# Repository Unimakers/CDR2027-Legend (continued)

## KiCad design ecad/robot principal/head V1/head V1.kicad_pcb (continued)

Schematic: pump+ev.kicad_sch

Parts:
C56, C57: 100nF; C_0805_2012Metric_Pad1.18x1.45mm_HandSolder
D15: SS14; D_SMA
IC2: RZ7889; SOIC127P600X175-8N; Manufacturer_Part_Number RZ7889
J29: pump+ev; Molex_KK-254_AE-6410-04A_1x04_P2.54mm_Vertical
Q1: AO3400A; SOT-23
R45: 270; R_0805_2012Metric_Pad1.20x1.40mm_HandSolder
R46: 10K; R_0805_2012Metric_Pad1.20x1.40mm_HandSolder

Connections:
+5VP2: D15.1 (K), J29.3; also elsewhere on the board
+12V1: C56.1, IC2.4 (VCC); also elsewhere on the board
/actionneurs/EV1: R45.2; also elsewhere on the board
/actionneurs/PuEv 1/ev-: D15.2 (A), J29.4, Q1.3 (D)
/actionneurs/PuEv 1/pumpA: C57.1, IC2.7 (BO_1), IC2.8 (BO_2), J29.1
/actionneurs/PuEv 1/pumpB: C57.2, IC2.5 (FO_1), IC2.6 (FO_2), J29.2
/actionneurs/pump1: IC2.2 (FI); also elsewhere on the board
GND: C56.2, IC2.1 (BI), IC2.3 (GND), Q1.2 (S), R46.2; also elsewhere on the board
unnamed: Q1.1 (G), R45.1, R46.1

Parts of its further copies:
C58, C59, C60, C61, C62, C63, C64, C65, C66, C67, C68, C69, C70, C71: 100nF; C_0805_2012Metric_Pad1.18x1.45mm_HandSolder
D16, D17, D18, D19, D20, D21, D22: SS14; D_SMA
IC3, IC4, IC5, IC6, IC7, IC8, IC9: RZ7889; SOIC127P600X175-8N; Manufacturer_Part_Number RZ7889
J30, J31, J32, J33, J34, J35, J36: pump+ev; Molex_KK-254_AE-6410-04A_1x04_P2.54mm_Vertical
Q2, Q3, Q4, Q5, Q6, Q7, Q8: AO3400A; SOT-23
R47, R49, R51, R53, R55, R57, R59: 270; R_0805_2012Metric_Pad1.20x1.40mm_HandSolder
R48, R50, R52, R54, R56, R58, R60: 10K; R_0805_2012Metric_Pad1.20x1.40mm_HandSolder

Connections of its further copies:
+5VP2: D16.1 (K), D17.1 (K), D18.1 (K), D19.1 (K), D20.1 (K), D21.1 (K), D22.1 (K), J30.3, J31.3, J32.3, J33.3, J34.3, J35.3, J36.3; also elsewhere on the board
+12V1: C58.1, C60.1, C62.1, C64.1, C66.1, C68.1, C70.1, IC3.4 (VCC), IC4.4 (VCC), IC5.4 (VCC), IC6.4 (VCC), IC7.4 (VCC), IC8.4 (VCC), IC9.4 (VCC); also elsewhere on the board
/actionneurs/EV2: R47.2; also elsewhere on the board
/actionneurs/EV3: R49.2; also elsewhere on the board
/actionneurs/EV4: R51.2; also elsewhere on the board
/actionneurs/EV5: R53.2; also elsewhere on the board
/actionneurs/EV6: R55.2; also elsewhere on the board
/actionneurs/EV7: R57.2; also elsewhere on the board
/actionneurs/EV8: R59.2; also elsewhere on the board
/actionneurs/PuEv 2/ev-: D16.2 (A), J30.4, Q2.3 (D)
/actionneurs/PuEv 2/pumpA: C59.1, IC3.7 (BO_1), IC3.8 (BO_2), J30.1
/actionneurs/PuEv 2/pumpB: C59.2, IC3.5 (FO_1), IC3.6 (FO_2), J30.2
/actionneurs/PuEv 3/ev-: D17.2 (A), J31.4, Q3.3 (D)
/actionneurs/PuEv 3/pumpA: C61.1, IC4.7 (BO_1), IC4.8 (BO_2), J31.1
/actionneurs/PuEv 3/pumpB: C61.2, IC4.5 (FO_1), IC4.6 (FO_2), J31.2
/actionneurs/PuEv 4/ev-: D18.2 (A), J32.4, Q4.3 (D)
/actionneurs/PuEv 4/pumpA: C63.1, IC5.7 (BO_1), IC5.8 (BO_2), J32.1
/actionneurs/PuEv 4/pumpB: C63.2, IC5.5 (FO_1), IC5.6 (FO_2), J32.2
/actionneurs/PuEv 5/ev-: D19.2 (A), J33.4, Q5.3 (D)
/actionneurs/PuEv 5/pumpA: C65.1, IC6.7 (BO_1), IC6.8 (BO_2), J33.1
/actionneurs/PuEv 5/pumpB: C65.2, IC6.5 (FO_1), IC6.6 (FO_2), J33.2
/actionneurs/PuEv 6/ev-: D20.2 (A), J34.4, Q6.3 (D)
/actionneurs/PuEv 6/pumpA: C67.1, IC7.7 (BO_1), IC7.8 (BO_2), J34.1
/actionneurs/PuEv 6/pumpB: C67.2, IC7.5 (FO_1), IC7.6 (FO_2), J34.2
/actionneurs/PuEv 7/ev-: D21.2 (A), J35.4, Q7.3 (D)
/actionneurs/PuEv 7/pumpA: C69.1, IC8.7 (BO_1), IC8.8 (BO_2), J35.1
/actionneurs/PuEv 7/pumpB: C69.2, IC8.5 (FO_1), IC8.6 (FO_2), J35.2
/actionneurs/PuEv 8/ev-: D22.2 (A), J36.4, Q8.3 (D)
/actionneurs/PuEv 8/pumpA: C71.1, IC9.7 (BO_1), IC9.8 (BO_2), J36.1
/actionneurs/PuEv 8/pumpB: C71.2, IC9.5 (FO_1), IC9.6 (FO_2), J36.2
/actionneurs/pump2: IC3.2 (FI); also elsewhere on the board
/actionneurs/pump3: IC4.2 (FI); also elsewhere on the board
/actionneurs/pump4: IC5.2 (FI); also elsewhere on the board
/actionneurs/pump5: IC6.2 (FI); also elsewhere on the board
/actionneurs/pump6: IC7.2 (FI); also elsewhere on the board
/actionneurs/pump7: IC8.2 (FI); also elsewhere on the board
/actionneurs/pump8: IC9.2 (FI); also elsewhere on the board
GND: C58.2, C60.2, C62.2, C64.2, C66.2, C68.2, C70.2, IC3.1 (BI), IC3.3 (GND), IC4.1 (BI), IC4.3 (GND), IC5.1 (BI), IC5.3 (GND), IC6.1 (BI), IC6.3 (GND), IC7.1 (BI), IC7.3 (GND), IC8.1 (BI), IC8.3 (GND), IC9.1 (BI), IC9.3 (GND), Q2.2 (S), Q3.2 (S), Q4.2 (S), Q5.2 (S), Q6.2 (S), Q7.2 (S), Q8.2 (S), R48.2, R50.2, R52.2, R54.2, R56.2, R58.2, R60.2; also elsewhere on the board
unnamed: Q2.1 (G), R47.1, R48.1
unnamed: Q3.1 (G), R49.1, R50.1
unnamed: Q4.1 (G), R51.1, R52.1
unnamed: Q5.1 (G), R53.1, R54.1
unnamed: Q6.1 (G), R55.1, R56.1
unnamed: Q7.1 (G), R57.1, R58.1
unnamed: Q8.1 (G), R59.1, R60.1

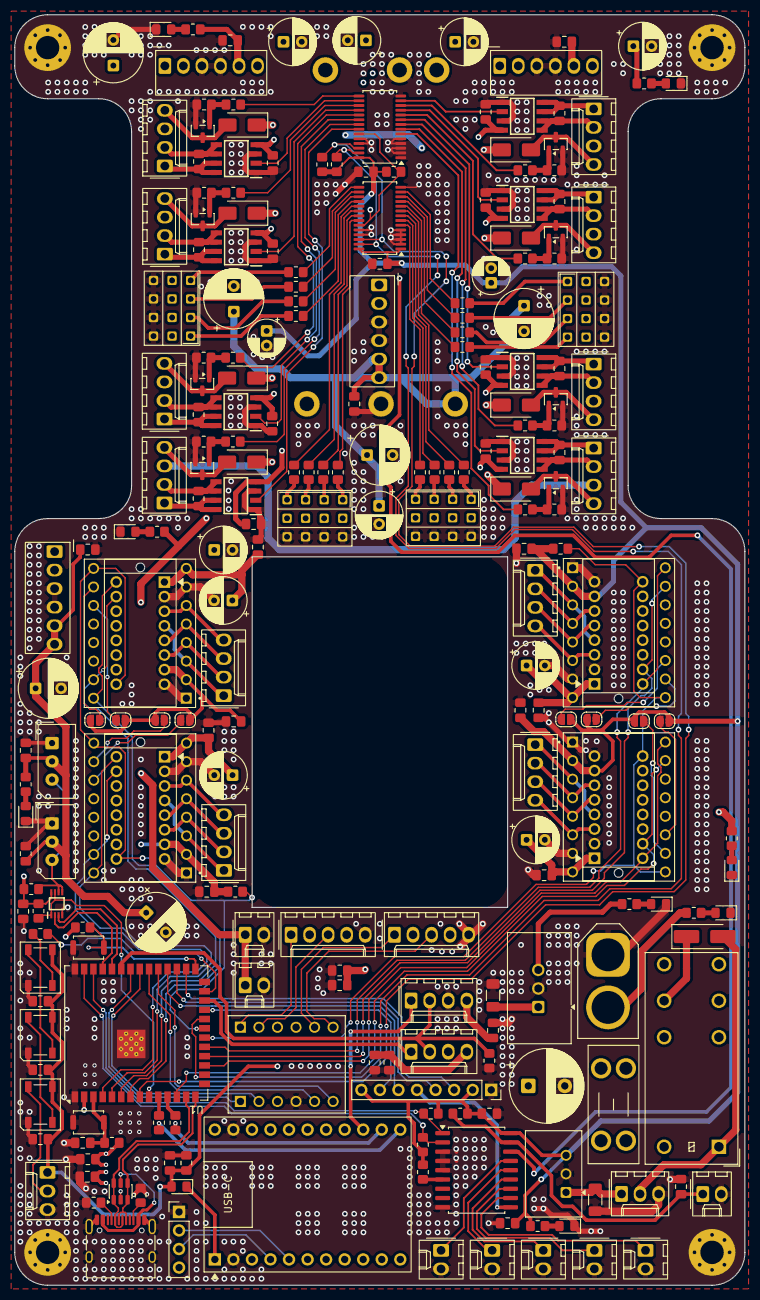
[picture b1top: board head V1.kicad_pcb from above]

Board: 4 copper layers, 100.0 x 174.0 mm, 241 parts (1 on the bottom side), 184 nets.

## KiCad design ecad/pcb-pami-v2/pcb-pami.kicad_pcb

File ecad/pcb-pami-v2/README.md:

# PCBete

Carte électronique des PAMI (petits robots autonomes) pour la Coupe de France de Robotique 2027.

Ce dossier contient la **nouvelle carte** (2 couches, simplifiée, en cours de conception). L'ancienne carte, celle des PAMI actuels, est dans l'historique Git (commit `070d910`, 2026-09-11) ; sa description est dans `.claude/skills/electronique-pami/SKILL.md`.

## Fonctions de la nouvelle carte (état du schéma, 2026-11-17)

Carte autour d'un ESP32-S3-WROOM-1 (empreinte WROOM-1U, antenne externe) :
- 2 NEMA 17 (28 V, 2 A max), 2 drivers TMC2209 SilentStepStick (U8, U9)
- 1 moteur DC (3 à 20 V, 3 A max) avec un driver RZ7899 (U1), un seul sens de rotation
- 2 servomoteurs 5 V (J23, J26)
- 1 capteur ToF VL53L0X en I2C (J2) et 1 MPU en I2C (MPU1)
- 1 écran TFT en SPI (J3)
- 1 module radio RFM69HCW en SPI (J17, empreinte à créer)
- LED NeoPixel embarquée (D6) et connecteur pour une guirlande (J8, 60 mA/LED)
- Arrêt d'urgence de puissance (30 V, 12 A max) par P-MOS commandé depuis J9
- Bouton d'équipe jaune/bleu (J5) et tirette de lancement (J7)
- USB-C (J1) pour la programmation seulement
- Tout est piloté directement par l'ESP32 : plus d'extenseur d'entrées/sorties (MCP23008)

Retiré par rapport à l'ancienne carte : MCP23008, 2 LTC4412 et leurs P-MOS, 2e driver DC, 3 des 4 ToF, capteurs AS5600, LiDAR (UART0), liaison Luckfox (UART1), mesure de la tension batterie.

## Format

- Carte **2 couches** (F.Cu et B.Cu, 1,6 mm), plus simple à router mais avec moins de place. Plus de plans internes.
- Contour **60 × 50 mm**, angles arrondis R3,5, de (30 ; 25) à (90 ; 75) dans KiCad. Pas de trou central.
- 4 trous M3 prévus (H1 à H4) ; H2 n'est pas encore posé dans le PCB.
- **Non routée** : placement en cours, 17 composants encore posés hors du contour (connecteurs J5, J7, J8, J9, J12, U1, PMOS du BAU, U4, condensateurs). Un second rectangle de 70 × 50 mm tracé sur Edge.Cuts en (25 ; 80) est vide.

## Alimentation

- Batterie LiPo 12 V (20 V max) sur XT30 (J6), puis coupure par le P-MOS AO4407A4 commandé par l'arrêt d'urgence (J9).
- Le 5 V est produit sur la carte par un buck AP63300 (3 A, entrée 3,8 à 32 V, après le BAU). Sortie réglée par R16/R17 : 0,8 × (1 + 27k/5,1k) = 5,04 V. Valeurs à vérifier sur la datasheet avant commande.
- Deux diodes SS34 font un OU entre le 5 V du buck (D3) et le 5 V de l'USB-C (D2) vers `VCC_5V_GLOBAL`. L'USB-C ne sert qu'à programmer sans batterie : en USB seul, le 5 V tombe vers 4,6 V.
- 3,3 V par un AMS1117-3.3 (U4).

## Reste à faire

- Relier à un GPIO de l'ESP32 : reset écran (`RST`), `TEAM_BTN`, `LAUNCHPULL`, `XSHUT0` et `GPIOX` du ToF, `EN` des TMC2209.
- Empreinte de J17 (radio), trou H2, finir le placement, puis router.
- Vérifier la LED D1 (valeur vide), l'empreinte de L1 (XAL5050-682MEC prévue) et la ligne DATA du NeoPixel sur J8.

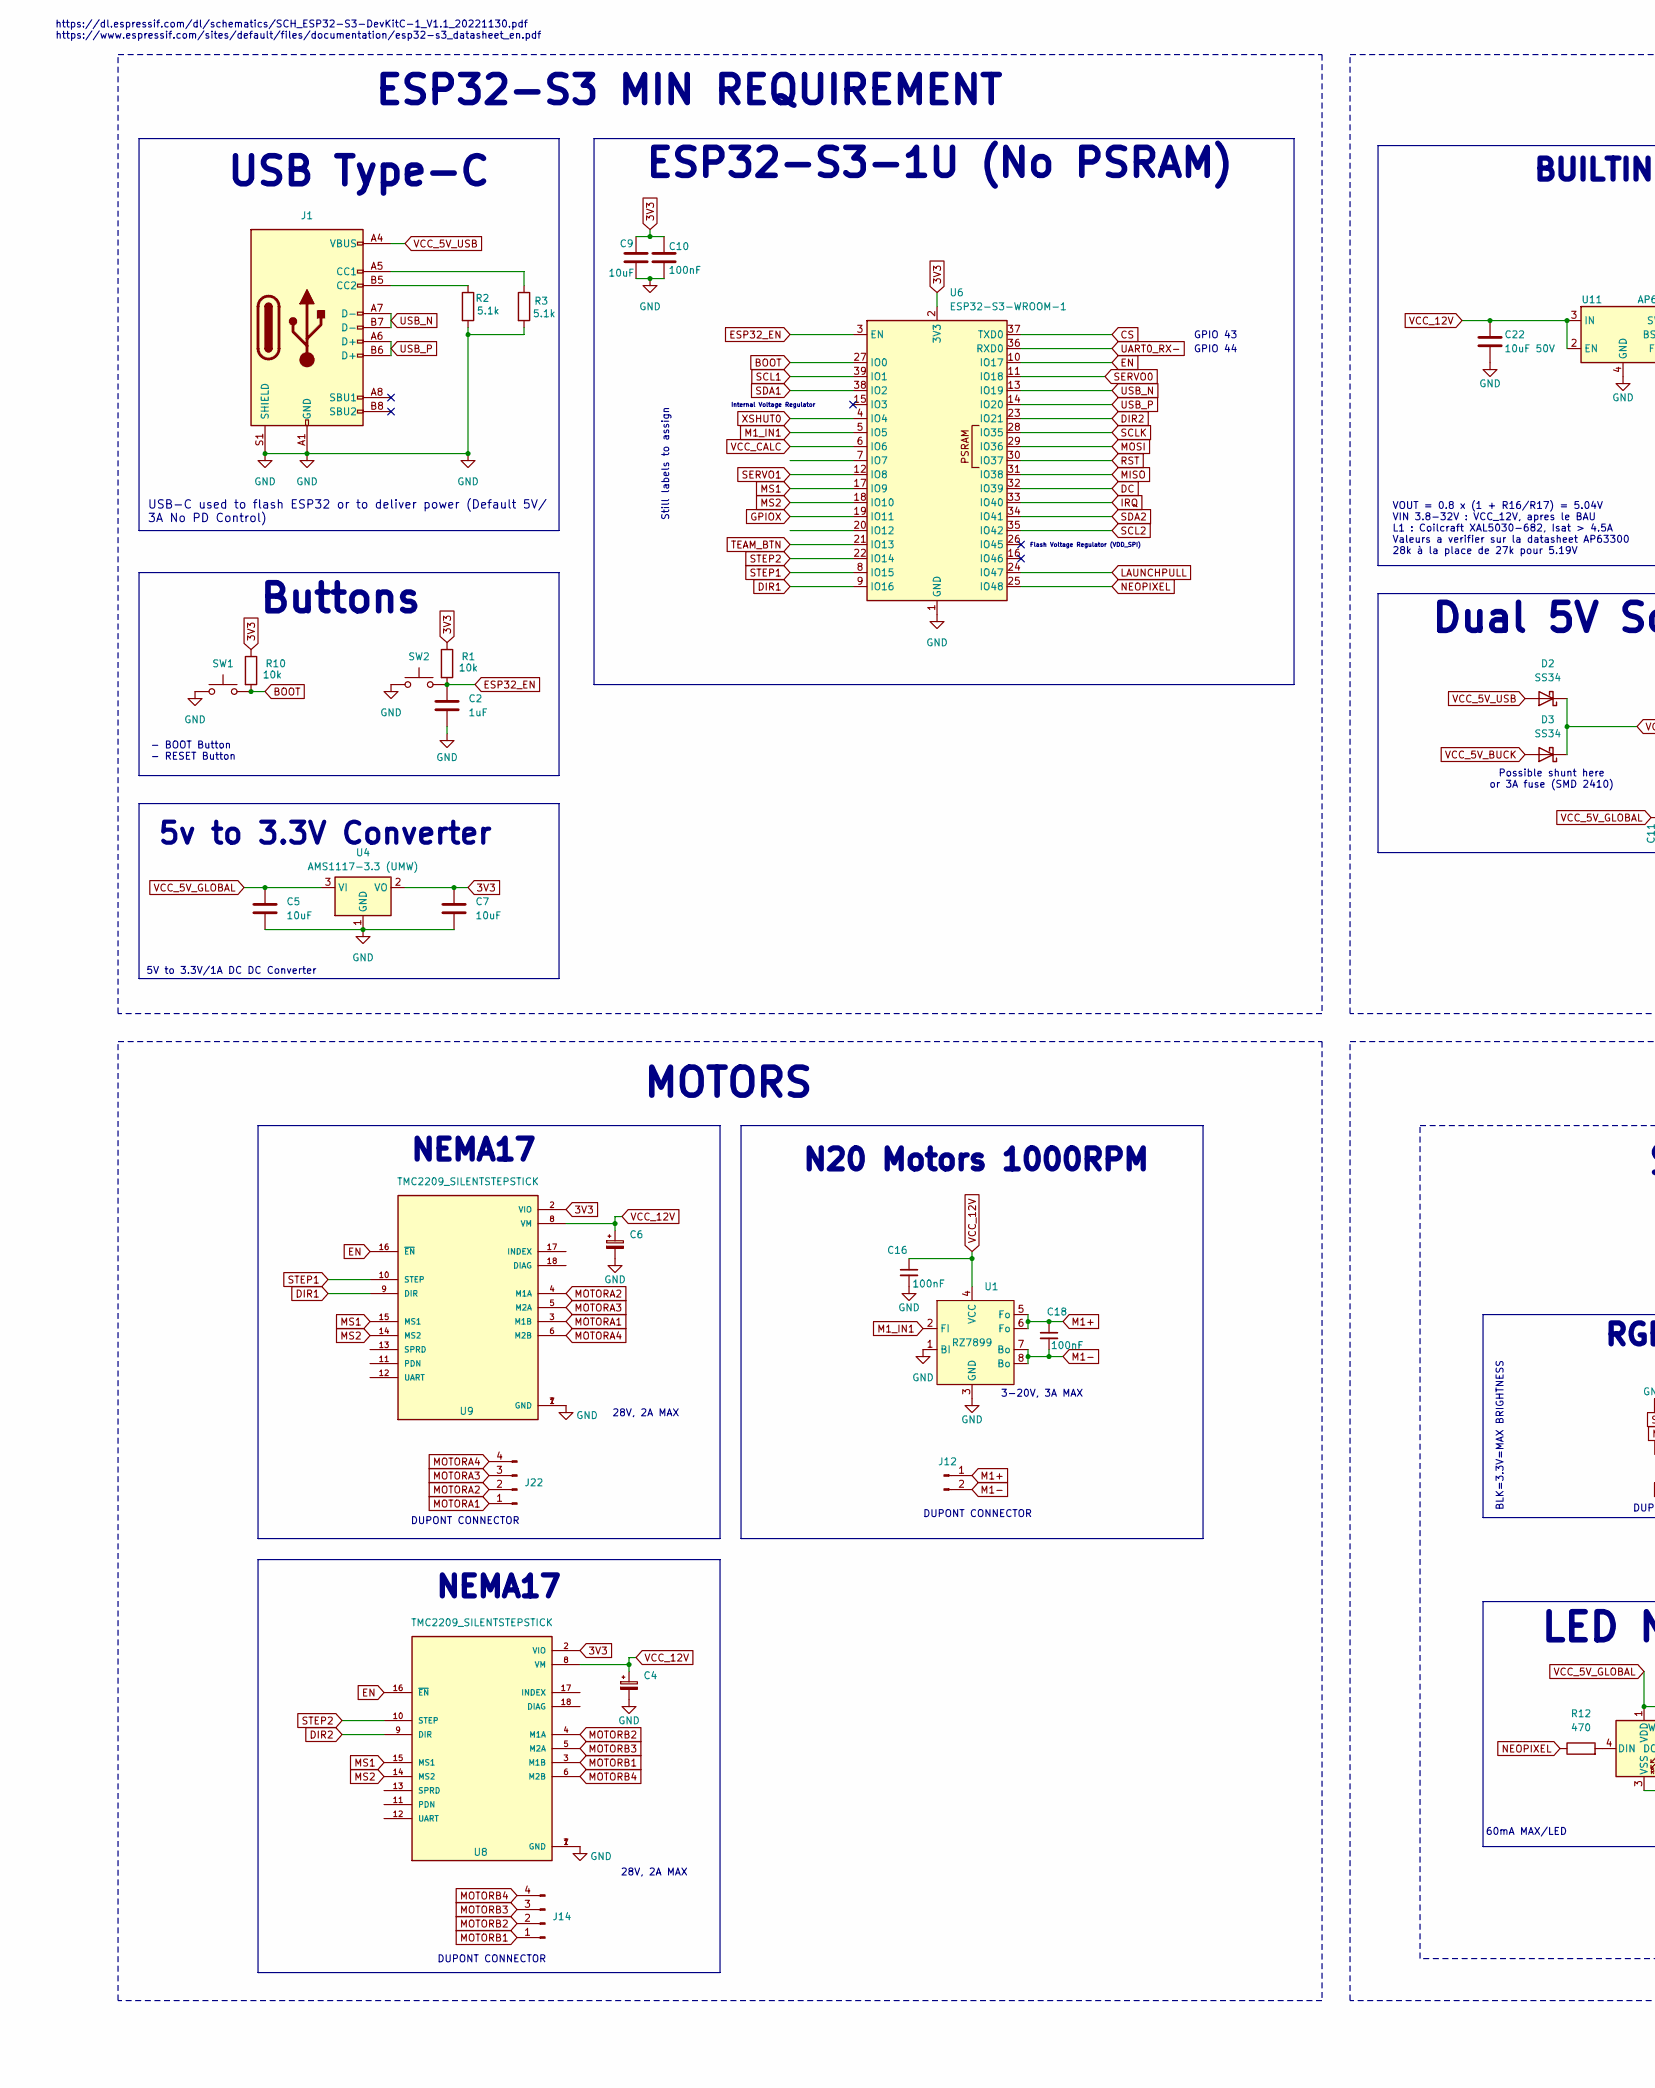
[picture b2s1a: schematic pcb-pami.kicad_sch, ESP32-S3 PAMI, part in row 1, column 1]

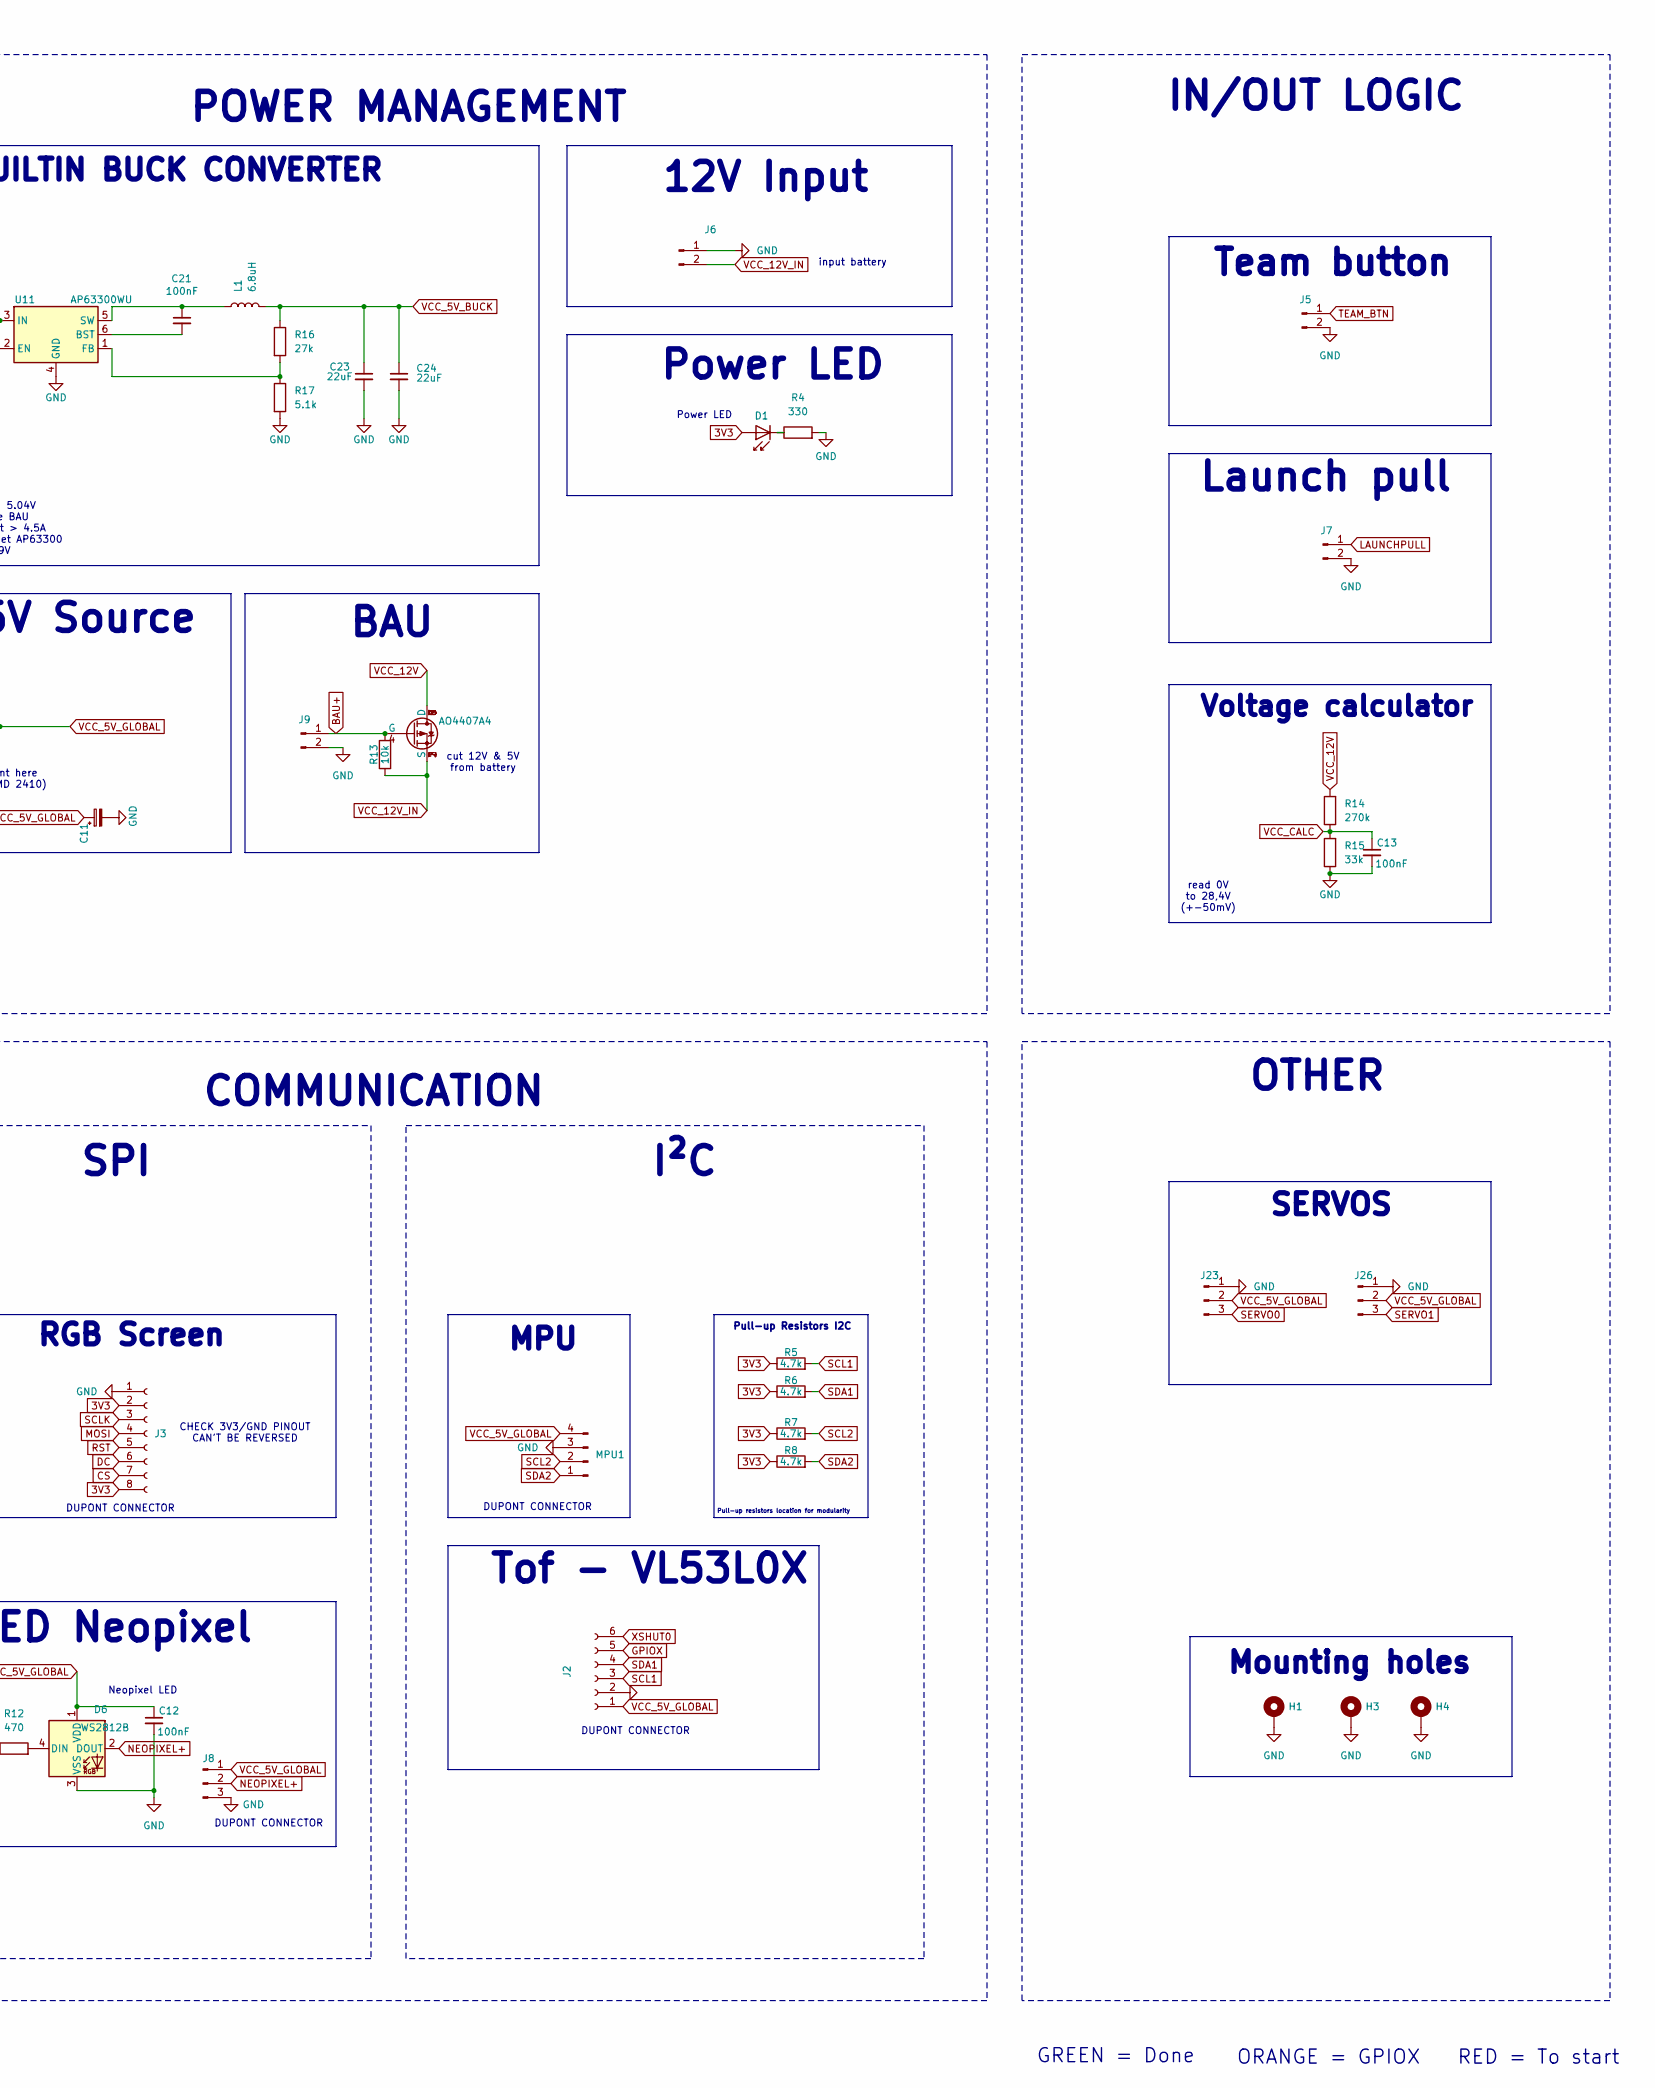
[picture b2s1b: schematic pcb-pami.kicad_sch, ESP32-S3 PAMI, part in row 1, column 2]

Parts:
AO4407A4: PMOS; SOIC-8-1EP_3.9x4.9mm_P1.27mm_EP2.29x3mm_ThermalVias
C2: 1uF; C_0805_2012Metric_Pad1.18x1.45mm_HandSolder
C4, C6: 100u; C_Radial_D8.0mm_H11.5mm_P3.50mm
C5, C7, C9: 10uF; C_0805_2012Metric_Pad1.18x1.45mm_HandSolder
C10, C12, C13, C16, C18, C21: 100nF; C_0805_2012Metric_Pad1.18x1.45mm_HandSolder
C11: 470u; C_Radial_D8.0mm_H11.5mm_P3.50mm
C22: 10uF 50V; C_1206_3216Metric_Pad1.33x1.80mm_HandSolder
C23, C24: 22uF; C_1206_3216Metric_Pad1.33x1.80mm_HandSolder
D1: LED_0805_2012Metric_Pad1.15x1.40mm_HandSolder
D2, D3: SS34; D_SMA
D6: WS2812B; LED_WS2812B_PLCC4_5.0x5.0mm_P3.2mm
H1, H3, H4: MountingHole_Pad; MountingHole_3.2mm_M3_Pad
J1: USB_C_Receptacle_USB2.0_16P; USB_C_Receptacle_GCT_USB4105-xx-A_16P_TopMnt_Horizontal
J2: Conn_01x06_Socket; PinHeader_1x06_P2.54mm_Vertical
J3: Conn_01x08_Socket; PinSocket_1x08_P2.54mm_Vertical
J5, J7, J9, J12: Conn_01x02_Pin; PinHeader_1x02_P2.54mm_Vertical
J6: Conn_01x02_Pin; AMASS_XT30U-F_1x02_P5.0mm_Vertical
J8, J23, J26: Conn_01x03_Pin; PinHeader_1x03_P2.54mm_Vertical
J14, J22: Conn_01x04_Pin; PinHeader_1x04_P2.54mm_Vertical
L1: 6.8uH; L_Coilcraft_XAL5030-XXX
MPU1: Conn_01x04_Pin; PinHeader_1x04_P2.54mm_Vertical
R1, R10, R13: 10k; R_0805_2012Metric_Pad1.20x1.40mm_HandSolder
R2, R3, R17: 5.1k; R_0805_2012Metric_Pad1.20x1.40mm_HandSolder
R4: 330; R_0805_2012Metric_Pad1.20x1.40mm_HandSolder
R5, R6, R7, R8: 4.7k; R_0805_2012Metric_Pad1.20x1.40mm_HandSolder
R12: 470; R_0805_2012Metric_Pad1.20x1.40mm_HandSolder
R14: 270k; R_0805_2012Metric_Pad1.20x1.40mm_HandSolder
R15: 33k; R_0805_2012Metric_Pad1.20x1.40mm_HandSolder
R16: 27k; R_0805_2012Metric_Pad1.20x1.40mm_HandSolder
SW1, SW2: SW_Push; SW_Push_SPST_NO_Alps_SKRK
U1: RZ7899; SOIC-8_3.9x4.9mm_P1.27mm
U4: AMS1117-3.3 (UMW); SOT-223-3_TabPin2
U6: ESP32-S3-WROOM-1; ESP32-S3-WROOM-1U
U8, U9: TMC2209_SILENTSTEPSTICK; MODULE_TMC2209_SILENTSTEPSTICK; PARTREV 1.20
U11: AP63300WU; TSOT-23-6

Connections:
3V3: C7.1, C9.1, C10.1, D1.2 (A), J3.2, J3.8, R1.1, R5.1, R6.1, R7.1, R8.1, R10.1, U4.2 (VO), U6.2 (3V3), U8.2 (VIO), U9.2 (VIO)
BAU+: AO4407A4.4 (G), J9.1, R13.2
BOOT: R10.2, SW1.2, U6.27 (IO0)
CS: J3.7, U6.37 (TXD0)
DC: J3.6, U6.32 (IO39)
DIR1: U6.9 (IO16), U9.9 (DIR)
DIR2: U6.23 (IO21), U8.9 (DIR)
EN: U6.10 (IO17), U8.16 (~EN), U9.16 (~EN)
ESP32_EN: C2.1, R1.2, SW2.2, U6.3 (EN)
GND: C2.2, C4.2, C5.2, C6.2, C7.2, C9.2, C10.2, C11.2, C12.2, C13.2, C16.2, C22.2, C23.2, C24.2, D6.3 (VSS), H1.1 (1_1), H3.1 (1_1), H4.1 (1_1), J1.A1 (GND), J1.A12 (GND), J1.B1 (GND), J1.B12 (GND), J1.S1 (SHIELD), J2.2, J3.1, J5.2, J6.1, J7.2, J8.3, J9.2, J23.1, J26.1, MPU1.3, R2.2, R3.2, R4.2, R15.1, R17.2, SW1.1, SW2.1, U1.1 (BI), U1.3 (GND), U4.1 (GND), U6.1 (GND), U6.40 (GND), U6.41 (GND), U8.1 (GND), U8.7 (GND), U9.1 (GND), U9.7 (GND), U11.4 (GND)
GPIOX: J2.5, U6.19 (IO11)
IRQ: U6.33 (IO40)
LAUNCHPULL: J7.1, U6.24 (IO47)
M1+: C18.1, J12.1, U1.5 (Fo), U1.6 (Fo)
M1-: C18.2, J12.2, U1.7 (Bo), U1.8 (Bo)
M1_IN1: U1.2 (FI), U6.5 (IO5)
MISO: U6.31 (IO38)
MOSI: J3.4, U6.29 (IO36)
MOTORA1: J22.1, U9.3 (M1B)
MOTORA2: J22.2, U9.4 (M1A)
MOTORA3: J22.3, U9.5 (M2A)
MOTORA4: J22.4, U9.6 (M2B)
MOTORB1: J14.1, U8.3 (M1B)
MOTORB2: J14.2, U8.4 (M1A)
MOTORB3: J14.3, U8.5 (M2A)
MOTORB4: J14.4, U8.6 (M2B)
MS1: U6.17 (IO9), U8.15 (MS1), U9.15 (MS1)
MS2: U6.18 (IO10), U8.14 (MS2), U9.14 (MS2)
NEOPIXEL: R12.1, U6.25 (IO48)
NEOPIXEL+: D6.2 (DOUT), J8.2
unnamed: D1.1 (K), R4.1
unnamed: D6.4 (DIN), R12.2
unnamed: J1.A5 (CC1), R3.1
unnamed: J1.B5 (CC2), R2.1
unnamed: C21.2, U11.6 (BST)
unnamed: R16.2, R17.1, U11.1 (FB)
unnamed: C21.1, L1.1, U11.5 (SW)
RST: J3.5, U6.30 (IO37)
SCL1: J2.3, R5.2, U6.39 (IO1)
SCL2: MPU1.2, R7.2, U6.35 (IO42)
SCLK: J3.3, U6.28 (IO35)
SDA1: J2.4, R6.2, U6.38 (IO2)
SDA2: MPU1.1, R8.2, U6.34 (IO41)
SERVO0: J23.3, U6.11 (IO18)
SERVO1: J26.3, U6.12 (IO8)
STEP1: U6.8 (IO15), U9.10 (STEP)
STEP2: U6.22 (IO14), U8.10 (STEP)
TEAM_BTN: J5.1, U6.21 (IO13)
UART0_RX-: U6.36 (RXD0)
USB_N: J1.A7 (D-), J1.B7 (D-), U6.13 (IO19)
USB_P: J1.A6 (D+), J1.B6 (D+), U6.14 (IO20)
VCC_5V_BUCK: C23.1, C24.1, D3.2 (A), L1.2, R16.1
VCC_5V_GLOBAL: C5.1, C11.1, C12.1, D2.1 (K), D3.1 (K), D6.1 (VDD), J2.1, J8.1, J23.2, J26.2, MPU1.4, U4.3 (VI)
VCC_5V_USB: D2.2 (A), J1.A4 (VBUS), J1.A9 (VBUS), J1.B4 (VBUS), J1.B9 (VBUS)
VCC_12V: AO4407A4.5 (D), AO4407A4.6 (D), AO4407A4.7 (D), AO4407A4.8 (D), AO4407A4.9 (D), C4.1, C6.1, C16.1, C22.1, R14.2, U1.4 (VCC), U8.8 (VM), U9.8 (VM), U11.2 (EN), U11.3 (IN)
VCC_12V_IN: AO4407A4.1 (S), AO4407A4.2 (S), AO4407A4.3 (S), J6.2, R13.1
VCC_CALC: C13.1, R14.1, R15.2, U6.6 (IO6)
XSHUT0: J2.6, U6.4 (IO4)

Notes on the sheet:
USB-C used to flash ESP32 or to deliver power (Default 5V/ 3A No PD Control)
Pull-up Resistors I2C
read 0V to 28,4V (+-50mV)
Power LED
LED Neopixel
MOTORS
DUPONT CONNECTOR
IN/OUT LOGIC
Buttons
GREEN = Done
BUILTIN BUCK CONVERTER
CHECK 3V3/GND PINOUT CAN'T BE REVERSED
ESP32-S3-1U (No PSRAM)
RED = To start
BAU
Dual 5V Source
28V, 2A MAX
USB Type-C
5v to 3.3V Converter
5V to 3.3V/1A DC DC Converter
https://www.espressif.com/sites/default/files/documentation/esp32-s3_datasheet_en.pdf
NEMA17
Neopixel LED
GPIO 44
3-20V, 3A MAX
VOUT = 0.8 x (1 + R16/R17) = 5.04V VIN 3.8-32V : VCC_12V, apres le BAU L1 : Coilcraft XAL5030-682, Isat > 4.5A Valeurs a verifier sur la datasheet AP63300 28k à la place de 27k pour 5.19V
Pull-up resistors location for modularity
ESP32-S3 MIN REQUIREMENT
cut 12V & 5V from battery
Flash Voltage Regulator (VDD_SPI)
60mA MAX/LED
N20 Motors 1000RPM
I²C
GPIO 43
SPI
Team button
Tof - VL53L0X
Possible shunt here or 3A fuse (SMD 2410)
ORANGE = GPIOX
Still labels to assign

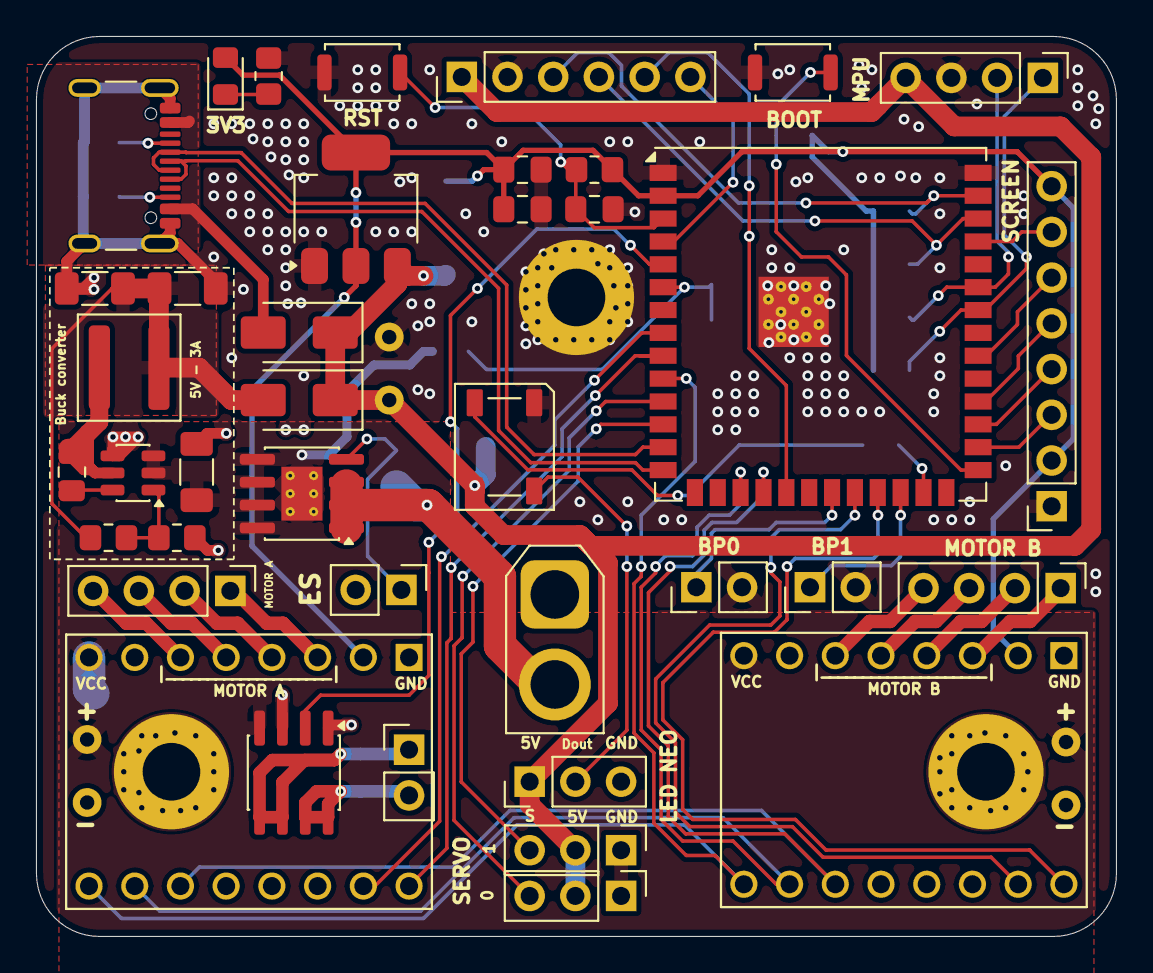
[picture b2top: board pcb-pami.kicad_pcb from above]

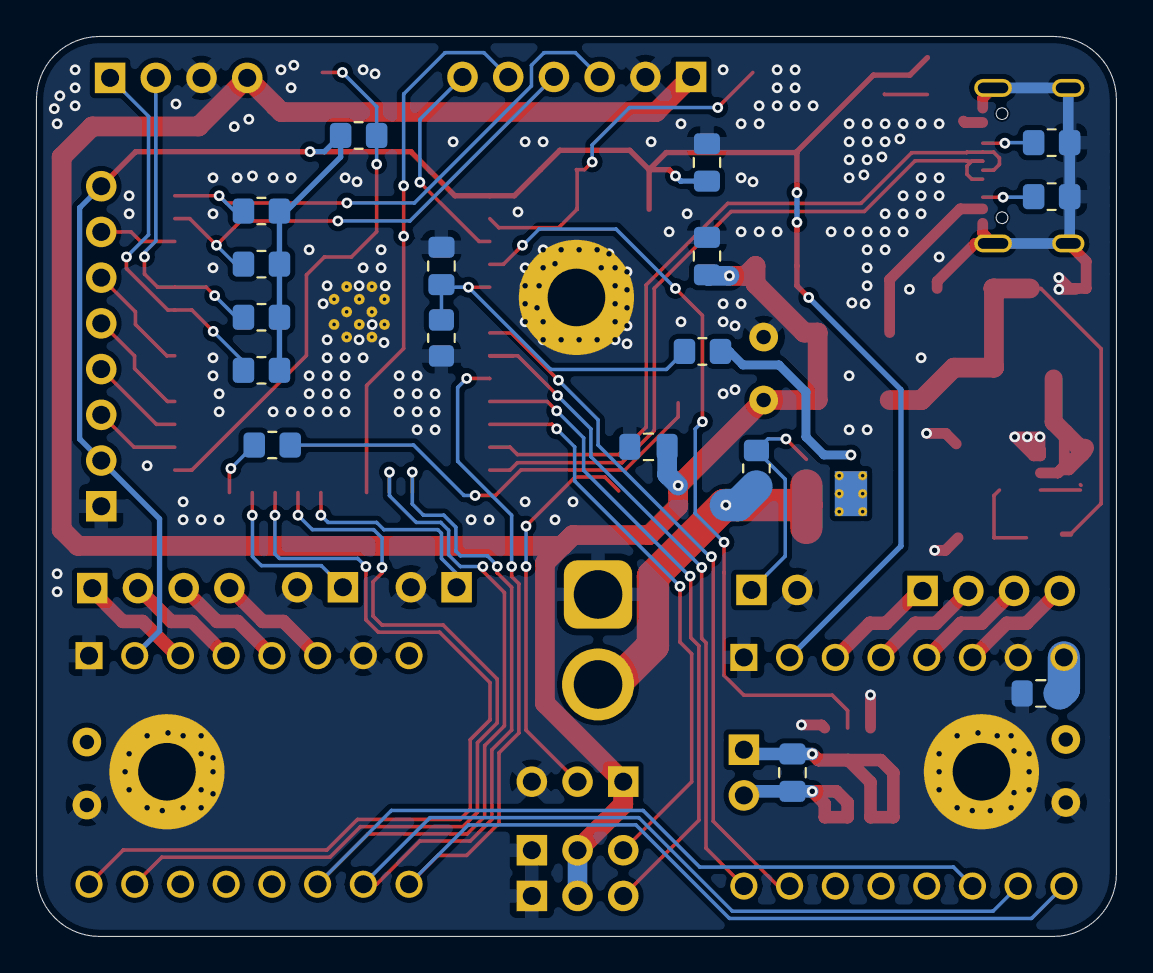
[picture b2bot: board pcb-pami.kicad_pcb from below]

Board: 2 copper layers, 60.0 x 50.0 mm, 62 parts (17 on the bottom side), 55 nets.

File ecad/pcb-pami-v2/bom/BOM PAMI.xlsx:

Nb de cartes | 13 |  | Marge appliquee seulement si 'Marge (1/0)' = 1 (resistances et condensateurs). 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
Marge R/C | 0.3
Inclure (1/0) | Refs | Valeur | Boitier | Type | Tolerance | Tension min (V) | Courant min (A) | Technologie / dielectrique | Autres contraintes | Qte/carte | Marge (1/0) | Qte a commander | Ref Mouser (a saisir) | Prix Mouser EUR | Total Mouser | Ref LCSC/JLC (a saisir) | Prix JLC USD | Total JLC | Remarque
1 | C2 | 1uF 50V X7R | 0805 | Condensateur | 10 % | 10 |  | X7R ou X5R | EN de l'ESP32 (3V3), avec R1 10k | 1 | 1 | 17 | 963-UMK212B7105KG-T | 0.099 | 1.683 |  |  |  | Taiyo Yuden 1uF 50V X7R 0805 ; stock 415 k (Mouser, 19/11/2026)
1 | C5,C7,C9 | 10uF 25V X5R | 0805 | Condensateur | 10 % | 10 |  | X5R ou X7R | Decouplage 5V/3V3 ; 16 V conseille | 3 | 1 | 51 | 963-TMK212BBJ106KG-T | 0.075 | 3.825 |  |  |  | Taiyo Yuden 10uF 25V X5R 0805 ; stock 240 k (Mouser, 19/11/2026)
1 | C10,C12,C13,C16,C21 | 100nF 50V X7R | 0805 | Condensateur | 10 % | 16 |  | X7R | Decouplage ; C21 = bootstrap du buck (BST) | 5 | 1 | 85 | 187-CL21B104KBCNNNC | 0.028 | 2.38 |  |  |  | Samsung 100nF 50V X7R 0805 ; stock 19 k (Mouser, 19/11/2026)
1 | C22 | 10uF 50V | 0805 | Condensateur | 10 % | 35 |  | X7R ou X5R | Entree buck (VIN 12 V, 20 V max) ; 50 V conseille (perte de capacite sous tensi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 | 1 | 1 | 17 | 963-UMK316BBJ106ML-T | 0.188 | 3.196 |  |  |  | EMPREINTE 1206 : Taiyo Yuden 10uF 50V X5R 1206 20 % ; stock 342 k. Les 10uF >=3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
1 | C23,C24 | 22uF 25V X5R | 0805 | Condensateur | 20 % | 10 |  | X5R ou X7R | Sortie buck 5 V ; 16 V conseille ; ESR bas | 2 | 1 | 34 | 963-TMK316BBJ226ML-T | 0.27 | 9.18 |  |  |  | EMPREINTE 1206 : Taiyo Yuden 22uF 25V X5R 1206 ; stock 102 k. En 0805, seul Tai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
1 | C4,C6 | 100uF >=35V radial D8 P3.5 | THT | Condensateur electrolytique | 20 % | 25 |  | Alu radial | Bus 12 V (20 V max) ; 35 V conseille ; D8 mm, H max 11.5 mm, pas 3.5 mm | 2 | 0 | 26 | 647-UPW1V101MPD | 0.204 | 5.304 |  |  |  | Nichicon UPW 100uF 35V 105C low-Z, D8 x 11.5, pas 3.5 (verifie), vrac ; stock 5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
1 | C11 | 470uF >=10V radial D8 P3.5 | THT | Condensateur electrolytique | 20 % | 10 |  | Alu radial | Bus 5 V ; 16 V conseille ; D8 mm, H max 11.5 mm, pas 3.5 mm | 1 | 0 | 13 | 647-UVR1C471MPD1TD | 0.167 | 2.171 |  |  |  | Nichicon UVR 470uF 16V 85C, D8 x 11.5, pas 3.5 (verifie) ; stock 4 742. Version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
1 | D2,D3 | SS34 Schottky 40V 3A | SMA | Diode Schottky |  | 20 | 3 | Schottky | OU de sources 5 V (USB / buck) ; Vrrm >= 20 V (40 V conseille), If >= 3 A, Vf b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 | 2 | 0 | 26 | 821-SS34 | 0.339 | 8.814 |  |  |  | Taiwan Semi SS34 40V 3A SMA ; stock 5 167. Moins cher : 512-SS34FA (0.313 EUR) 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
1 | L1 | 6.8uH 6.4A XAL5050-682MEC | XAL5050 | Inductance de puissance | 20 % |  | 4 | Blindee | 6.8 uH ; Isat >= 4 A, Irms >= 3 A, DCR bas ; empreinte XAL5030 a verifier | 1 | 0 | 13 | 652-SRP6030VA-6R8M | 1.06 | 13.78 |  |  |  | Bourns 6.8uH, Isat 6.5 A (verifie), 7.1 x 6.6 x 2.8 mm ; stock 1 331. EMPREINTE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
1 | R1,R10,R13 | 10k 1% | 0805 | Resistance | 1 % |  |  | Couche epaisse | 125 mW mini | 3 | 1 | 51 | 708-RMCF0805FT10K0 | 0.014 | 0.714 |  |  |  | Stackpole 10k 1% 0805 1/8W ; stock 1 M (Mouser, 19/11/2026)
1 | R2,R3,R17 | 5.1k 1% | 0805 | Resistance | 1 % |  |  | Couche epaisse | R2/R3 = CC USB-C (5.1 k 1 % impose) ; R17 = bas du FB du buck | 3 | 1 | 51 | 708-RMCF0805FT5K10 | 0.014 | 0.714 |  |  |  | Stackpole 5.1k 1% 0805 ; stock 40 k (Mouser, 19/11/2026)
1 | R4 | 330 1% | 0805 | Resistance | 1 % |  |  | Couche epaisse | Serie LED D1 (3V3) | 1 | 1 | 17 | 708-RMCF0805FT330R | 0.012 | 0.204 |  |  |  | Stackpole 330R 1% 0805 ; stock 46 k (Mouser, 19/11/2026)
1 | R5,R6,R7,R8 | 4.7k 1% | 0805 | Resistance | 1 % |  |  | Couche epaisse | Pull-ups I2C | 4 | 1 | 68 | 708-RMCF0805FT4K70 | 0.014 | 0.952 |  |  |  | Stackpole 4.7k 1% 0805 ; stock 272 k (Mouser, 19/11/2026)
1 | R12 | 470 1% | 0805 | Resistance | 1 % |  |  | Couche epaisse | Serie DIN NeoPixel | 1 | 1 | 17 | 708-RMCF0805FT470R | 0.014 | 0.238 |  |  |  | Stackpole 470R 1% 0805 ; stock 376 k (Mouser, 19/11/2026)
1 | R14 | 270k 1% | 0805 | Resistance | 1 % |  |  | Couche epaisse | Diviseur de mesure de tension (haut), a garder 1 % | 1 | 1 | 17 | 603-RC0805FR-07270KL | 0.016 | 0.272 |  |  |  | Yageo 270k 1% 0805 ; stock 14 k (Stackpole non trouve) (Mouser, 19/11/2026)
1 | R15 | 33k 1% | 0805 | Resistance | 1 % |  |  | Couche epaisse | Diviseur de mesure de tension (bas), a garder 1 % | 1 | 1 | 17 | 708-RMCF0805FT33K0 | 0.014 | 0.238 |  |  |  | Stackpole 33k 1% 0805 ; stock 41 k (Mouser, 19/11/2026)
1 | R16 | 27k 1% | 0805 | Resistance | 1 % |  |  | Couche epaisse | Retour FB du buck (haut), a garder 1 % : fixe le 5 V | 1 | 1 | 17 | 708-RMCF0805FT27K0 | 0.015 | 0.255 |  |  |  | Stackpole 27k 1% 0805 ; stock 29 k (Mouser, 19/11/2026)
1 | AO4407A4 | P-MOS 30V 12A (AO4407A) | SOIC-8 | MOSFET canal P |  | 30 | 12 | MOSFET P | Coupure BAU : Vds >= 30 V, Id >= 12 A, Vgs max >= 20 V, Rds(on) bas ; SOIC-8 (S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 | 1 | 0 | 13 | 78-SI4425FDY-T1-GE3 | 0.516 | 6.708 |  |  |  | SUBSTITUTION AO4407A (absent chez Mouser) : Vishay SI4425FDY P-MOS 30V 12.7A SO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
1 | U11 | AP63300WU-7 buck 3A | TSOT-23-6 | Convertisseur buck |  | 20 | 3 | Buck 12 V -> 5 V | Vin >= 20 V, Iout >= 3 A, Vref 0.8 V (diviseur R16/R17), TSOT-23-6 : brochage A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 | 1 | 0 | 13 | 621-AP63301WU-7 | 0.585 | 7.605 |  |  |  | SUBSTITUTION : AP63300WU-7 a 0 en stock (reassort mai 2027). AP63301 = meme boi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
1 | U6 | ESP32-S3-WROOM-1U-N8 | module SMD | Module ESP32 |  |  |  | ESP32-S3-WROOM-1U | Variante sans PSRAM octale (N4/N8/N16, pas R2/R8) : IO35-37 utilises ; antenne 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 | 1 | 0 | 13 | 356-ESP32S3WROOM1UN8 | 4.35 | 56.55 |  |  |  | Espressif ESP32-S3-WROOM-1U-N8 ; stock 189 (palier 10) (Mouser, 19/11/2026)
 |  |  |  |  |  |  |  |  |  |  |  |  |  | Totaux | 124.783 |  |  | 0
